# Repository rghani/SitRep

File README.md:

# SitRep

SitRep is a Workout Posture Correction System which uses a Microsoft Kinect to analyze a person's body when weightlifting, and informs the person which joint or limb needs to be corrected via an 8x10 LED Matrix.

Check out https://rayyanghani.com/projects/#/sitrep/ for a more detailed description of the project and photos.

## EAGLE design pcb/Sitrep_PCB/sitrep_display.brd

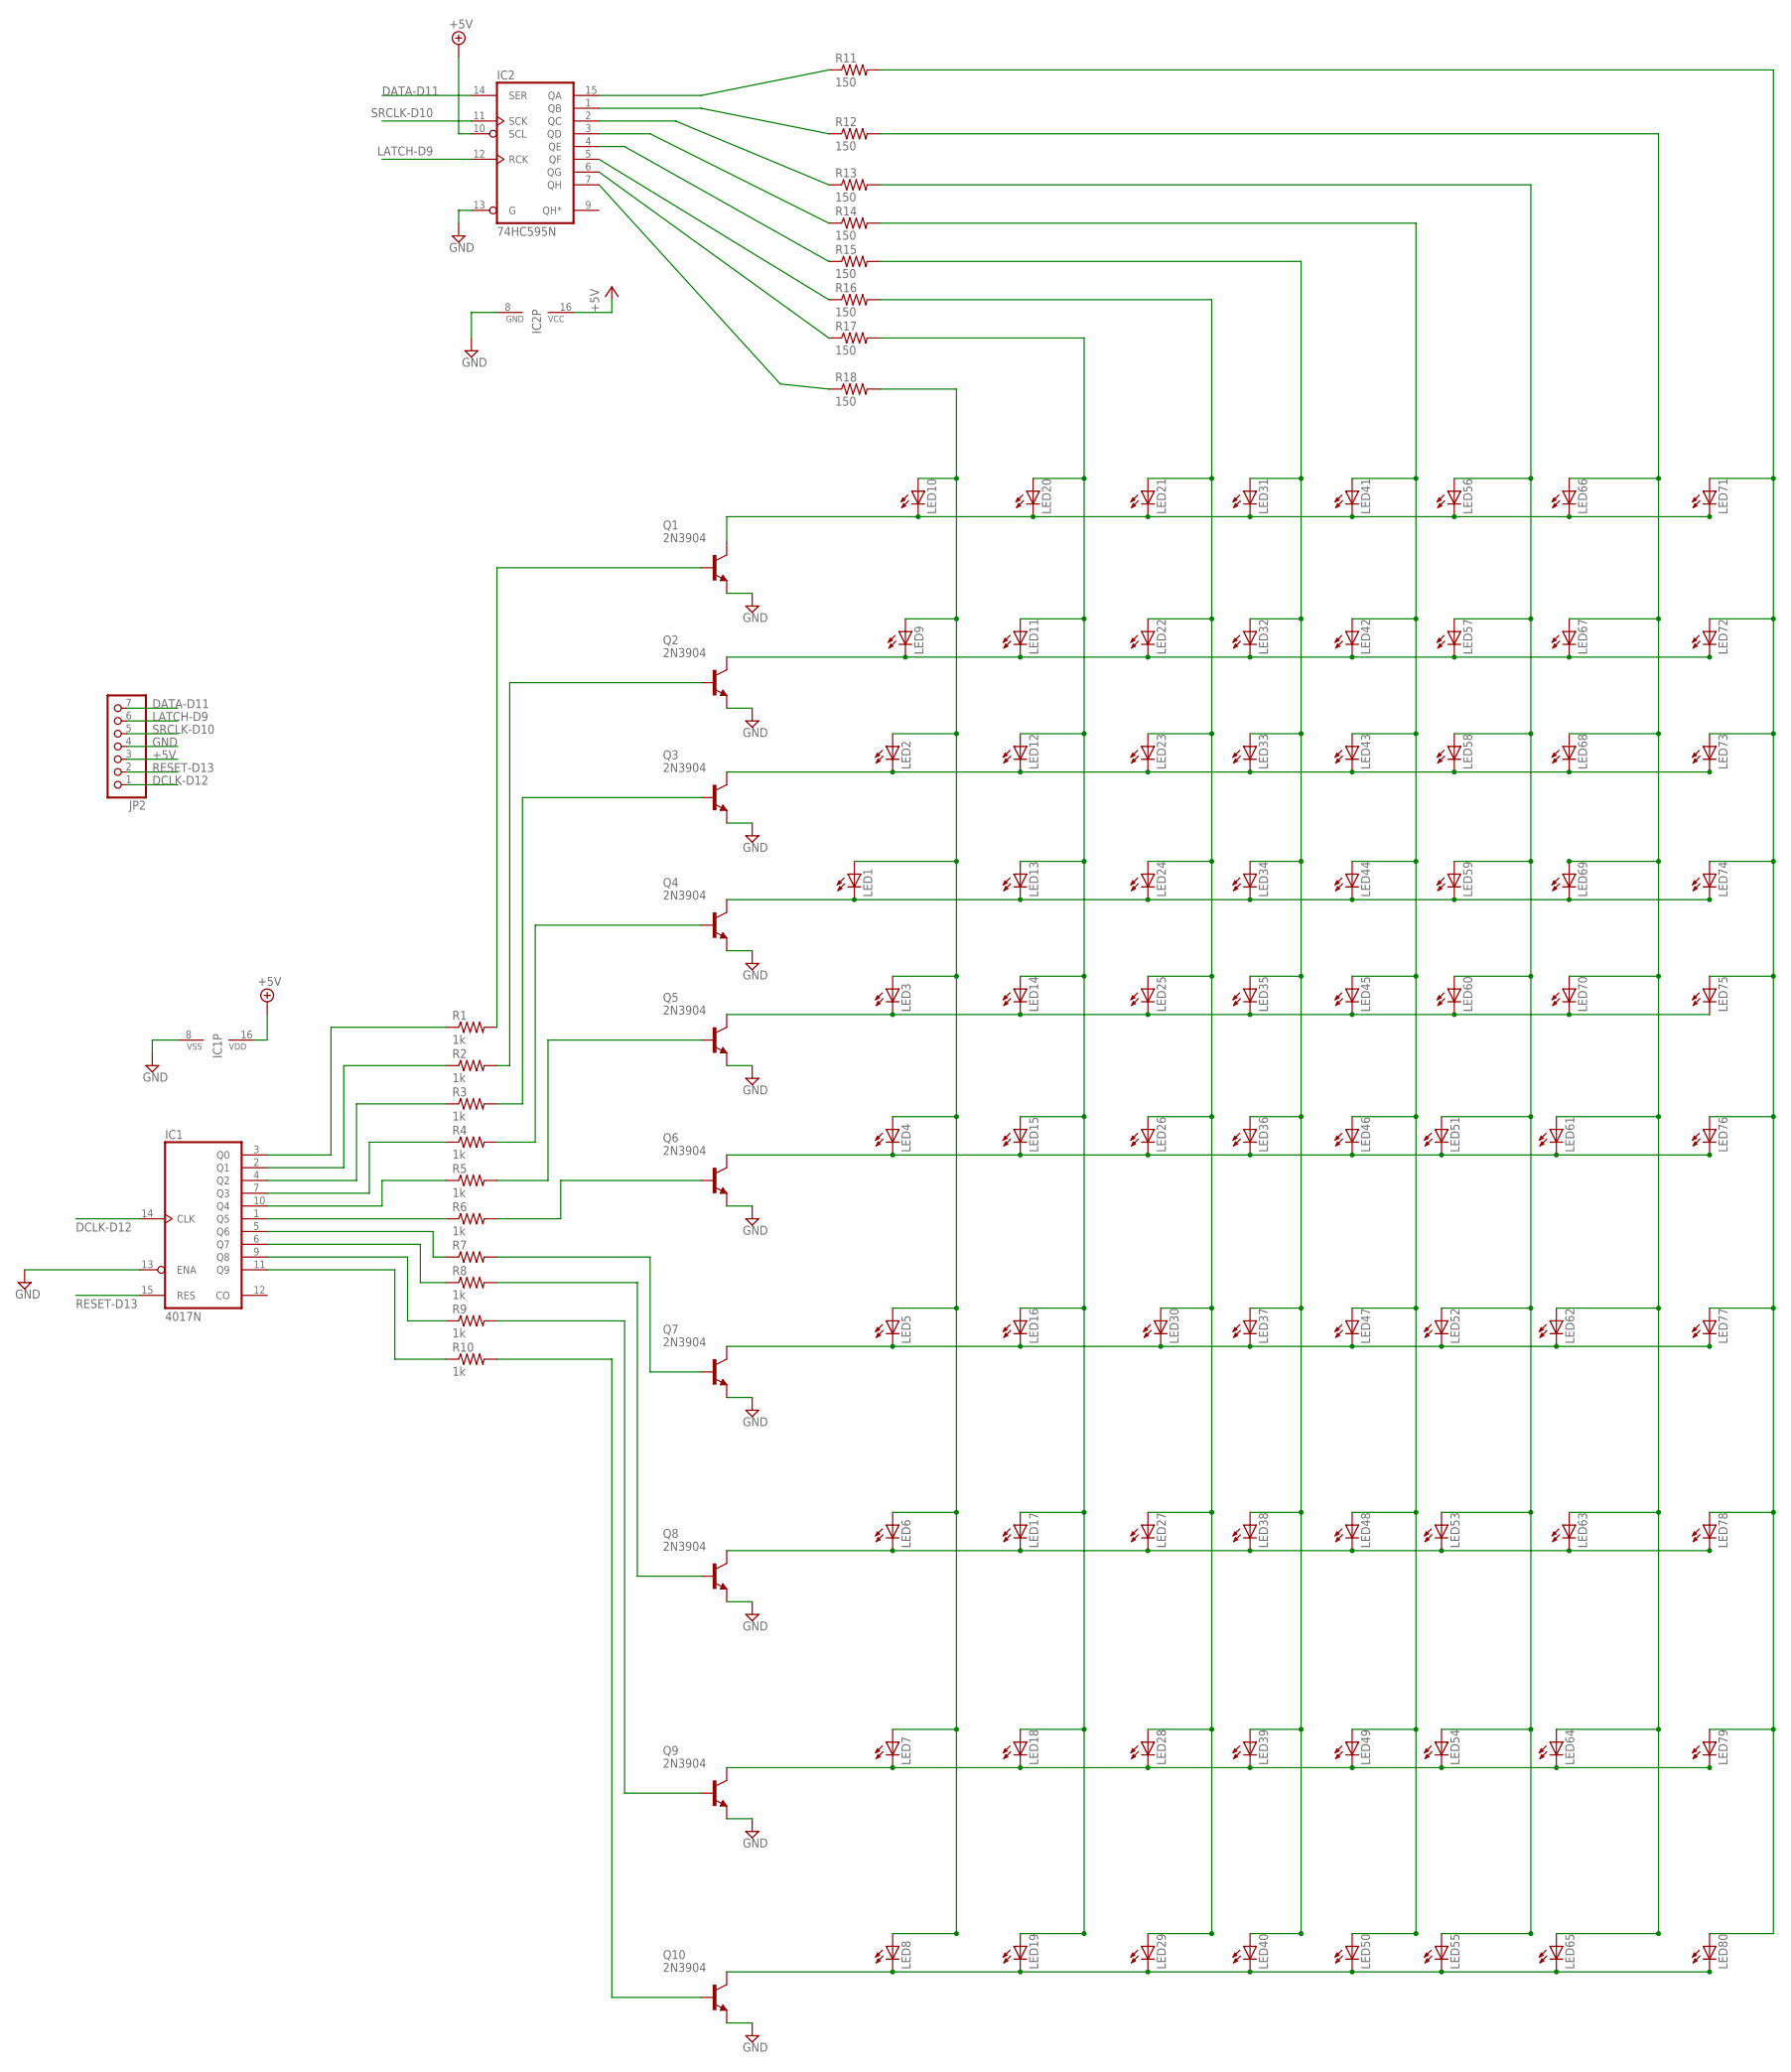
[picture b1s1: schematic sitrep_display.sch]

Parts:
IC1: 4017N; DIL16
IC2: 74HC595N; DIL16
JP2: PINHD-1X7/90; 1X07/90
LED1, LED2, LED3, LED4, LED5, LED6, LED7, LED8, LED9, LED10, LED11, LED12, LED13, LED14, LED15, LED16, LED17, LED18, LED19, LED20, LED21, LED22, LED23, LED24, LED25, LED26, LED27, LED28, LED29, LED30, LED31, LED32, LED33, LED34, LED35, LED36, LED37, LED38, LED39, LED40, LED41, LED42, LED43, LED44, LED45, LED46, LED47, LED48, LED49, LED50, LED51, LED52, LED53, LED54, LED55, LED56, LED57, LED58, LED59, LED60, LED61, LED62, LED63, LED64, LED65, LED66, LED67, LED68, LED69, LED70, LED71, LED72, LED73, LED74, LED75, LED76, LED77, LED78, LED79, LED80: LED5MM
Q1, Q2, Q3, Q4, Q5, Q6, Q7, Q8, Q9, Q10: 2N3904; TO92
R1, R2, R3, R4, R5, R6, R8, R9, R10: 1k; 0204V
R7: R-US_0204/2V; 0204V
R11, R12, R13, R14, R15, R16, R17, R18: 150; 0207/2V

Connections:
+5V: IC1.16 (VDD), IC2.10 (SCL), IC2.16 (VCC), JP2.3
DATA-D11: IC2.14 (SER), JP2.7
DCLK-D12: IC1.14 (CLK), JP2.1
GND: IC1.8 (VSS), IC1.13 (ENA), IC2.8 (GND), IC2.13 (G), JP2.4, Q1.3 (E), Q2.3 (E), Q3.3 (E), Q4.3 (E), Q5.3 (E), Q6.3 (E), Q7.3 (E), Q8.3 (E), Q9.3 (E), Q10.3 (E)
LATCH-D9: IC2.12 (RCK), JP2.6
unnamed: IC2.15 (QA), R11.1
unnamed: IC2.1 (QB), R12.1
unnamed: IC2.2 (QC), R13.1
unnamed: IC2.3 (QD), R14.1
unnamed: IC2.4 (QE), R15.1
unnamed: IC2.5 (QF), R16.1
unnamed: IC2.6 (QG), R17.1
unnamed: IC2.7 (QH), R18.1
unnamed: LED11.A, LED12.A, LED13.A, LED14.A, LED15.A, LED16.A, LED17.A, LED18.A, LED19.A, LED20.A, R17.2
unnamed: LED21.A, LED22.A, LED23.A, LED24.A, LED25.A, LED26.A, LED27.A, LED28.A, LED29.A, LED30.A, R16.2
unnamed: LED31.A, LED32.A, LED33.A, LED34.A, LED35.A, LED36.A, LED37.A, LED38.A, LED39.A, LED40.A, R15.2
unnamed: LED41.A, LED42.A, LED43.A, LED44.A, LED45.A, LED46.A, LED47.A, LED48.A, LED49.A, LED50.A, R14.2
unnamed: LED51.A, LED52.A, LED53.A, LED54.A, LED55.A, LED56.A, LED57.A, LED58.A, LED59.A, LED60.A, R13.2
unnamed: LED61.A, LED62.A, LED63.A, LED64.A, LED65.A, LED66.A, LED67.A, LED68.A, LED69.A, LED70.A, R12.2
unnamed: LED71.A, LED72.A, LED73.A, LED74.A, LED75.A, LED76.A, LED77.A, LED78.A, LED79.A, LED80.A, R11.2
unnamed: LED1.A, LED2.A, LED3.A, LED4.A, LED5.A, LED6.A, LED7.A, LED8.A, LED9.A, LED10.A, R18.2
unnamed: LED10.K (C), LED20.K (C), LED21.K (C), LED31.K (C), LED41.K (C), LED56.K (C), LED66.K (C), LED71.K (C), Q1.1 (C)
unnamed: LED9.K (C), LED11.K (C), LED22.K (C), LED32.K (C), LED42.K (C), LED57.K (C), LED67.K (C), LED72.K (C), Q2.1 (C)
unnamed: LED3.K (C), LED14.K (C), LED25.K (C), LED35.K (C), LED45.K (C), LED60.K (C), LED70.K (C), LED75.K (C), Q5.1 (C)
unnamed: LED1.K (C), LED13.K (C), LED24.K (C), LED34.K (C), LED44.K (C), LED59.K (C), LED69.K (C), LED74.K (C), Q4.1 (C)
unnamed: LED4.K (C), LED15.K (C), LED26.K (C), LED36.K (C), LED46.K (C), LED51.K (C), LED61.K (C), LED76.K (C), Q6.1 (C)
unnamed: LED5.K (C), LED16.K (C), LED30.K (C), LED37.K (C), LED47.K (C), LED52.K (C), LED62.K (C), LED77.K (C), Q7.1 (C)
unnamed: LED6.K (C), LED17.K (C), LED27.K (C), LED38.K (C), LED48.K (C), LED53.K (C), LED63.K (C), LED78.K (C), Q8.1 (C)
unnamed: LED2.K (C), LED12.K (C), LED23.K (C), LED33.K (C), LED43.K (C), LED58.K (C), LED68.K (C), LED73.K (C), Q3.1 (C)
unnamed: LED7.K (C), LED18.K (C), LED28.K (C), LED39.K (C), LED49.K (C), LED54.K (C), LED64.K (C), LED79.K (C), Q9.1 (C)
unnamed: LED8.K (C), LED19.K (C), LED29.K (C), LED40.K (C), LED50.K (C), LED55.K (C), LED65.K (C), LED80.K (C), Q10.1 (C)
unnamed: Q1.2 (B), R1.2
unnamed: Q2.2 (B), R2.2
unnamed: Q3.2 (B), R3.2
unnamed: Q4.2 (B), R4.2
unnamed: Q5.2 (B), R5.2
unnamed: Q6.2 (B), R6.2
unnamed: Q7.2 (B), R7.2
unnamed: Q8.2 (B), R8.2
unnamed: Q9.2 (B), R9.2
unnamed: Q10.2 (B), R10.2
unnamed: IC1.3 (Q0), R1.1
unnamed: IC1.2 (Q1), R2.1
unnamed: IC1.4 (Q2), R3.1
unnamed: IC1.7 (Q3), R4.1
unnamed: IC1.10 (Q4), R5.1
unnamed: IC1.1 (Q5), R6.1
unnamed: IC1.5 (Q6), R7.1
unnamed: IC1.6 (Q7), R8.1
unnamed: IC1.9 (Q8), R9.1
unnamed: IC1.11 (Q9), R10.1
RESET-D13: IC1.15 (RES), JP2.2
SRCLK-D10: IC2.11 (SCK), JP2.5

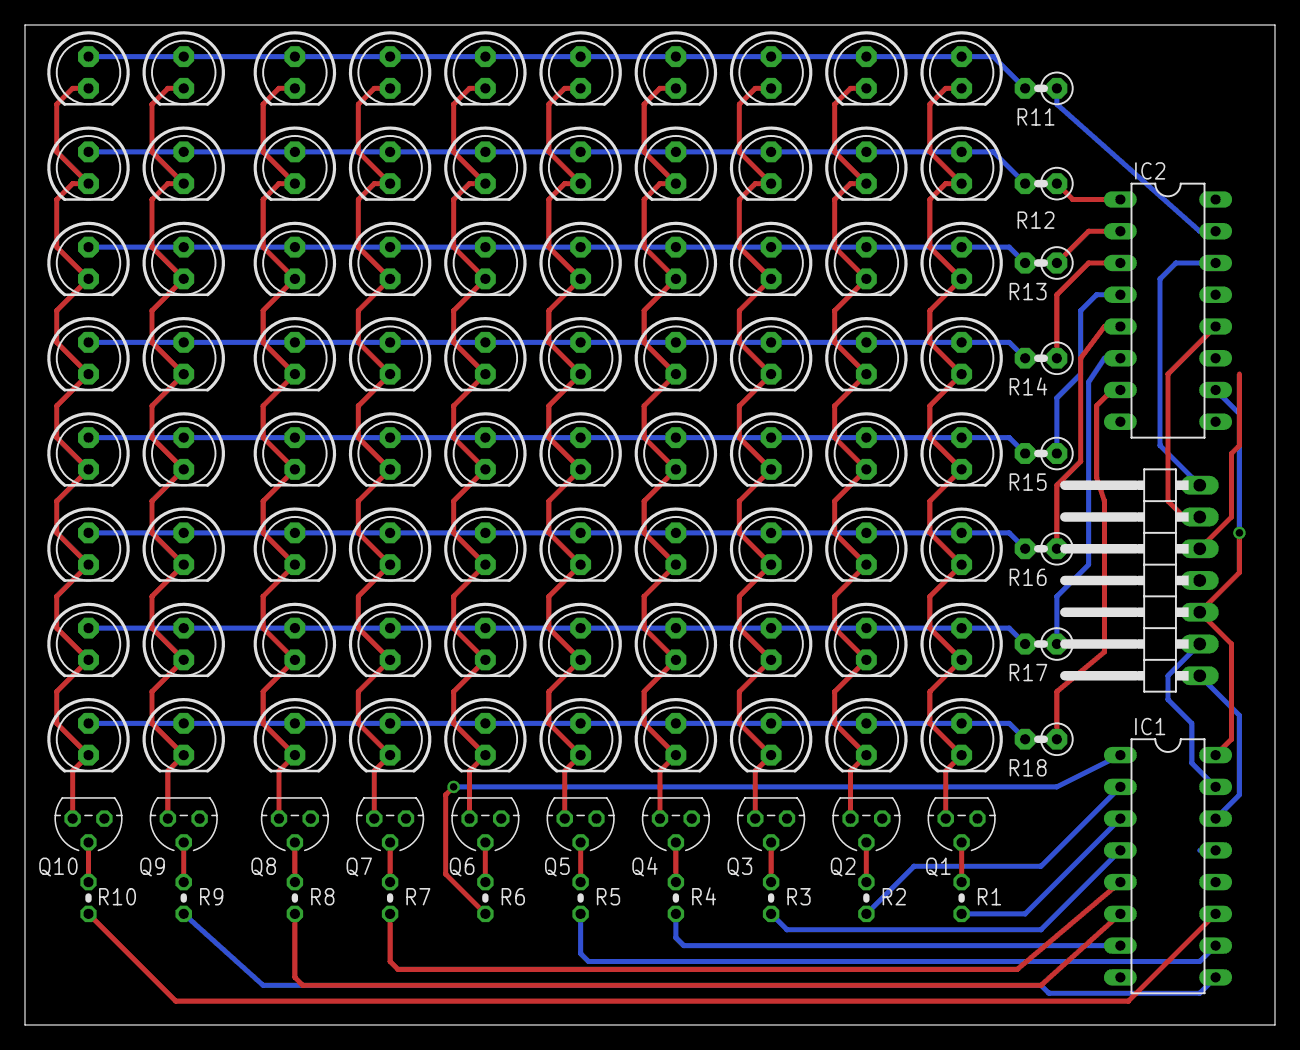
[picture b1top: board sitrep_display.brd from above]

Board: 2 copper layers, 100.0 x 80.0 mm, 111 parts (0 on the bottom side), 53 nets.

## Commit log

2016-10-30 Added gitignore
2016-10-30 Deleted incorrect gitignore file
2016-10-30 Readded correct gitignore file
2016-10-30 Adding files
2016-10-30 Developed event pipeline system
2016-11-03 Finished development of Particle Photon Event Pipeline
2016-11-06 Conducted end to end testing with event publishing, wrapped PublishEvent async method
2016-11-06 Enqueuing only occurs if data packets are different, 3 second min time limit on publishing
2016-11-07 Made Particle event publishing private
2016-11-08 Changed event publish data from bit vector to int
2016-11-08 Renamed arduino source code file
2016-11-08 New renamed arduino source code file
2017-01-01 Updated PCB files
2017-01-17 Added Particle Photon firmware

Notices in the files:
parts and their libraries:
Particle-Devices: Licensing: Designed by Particle.
